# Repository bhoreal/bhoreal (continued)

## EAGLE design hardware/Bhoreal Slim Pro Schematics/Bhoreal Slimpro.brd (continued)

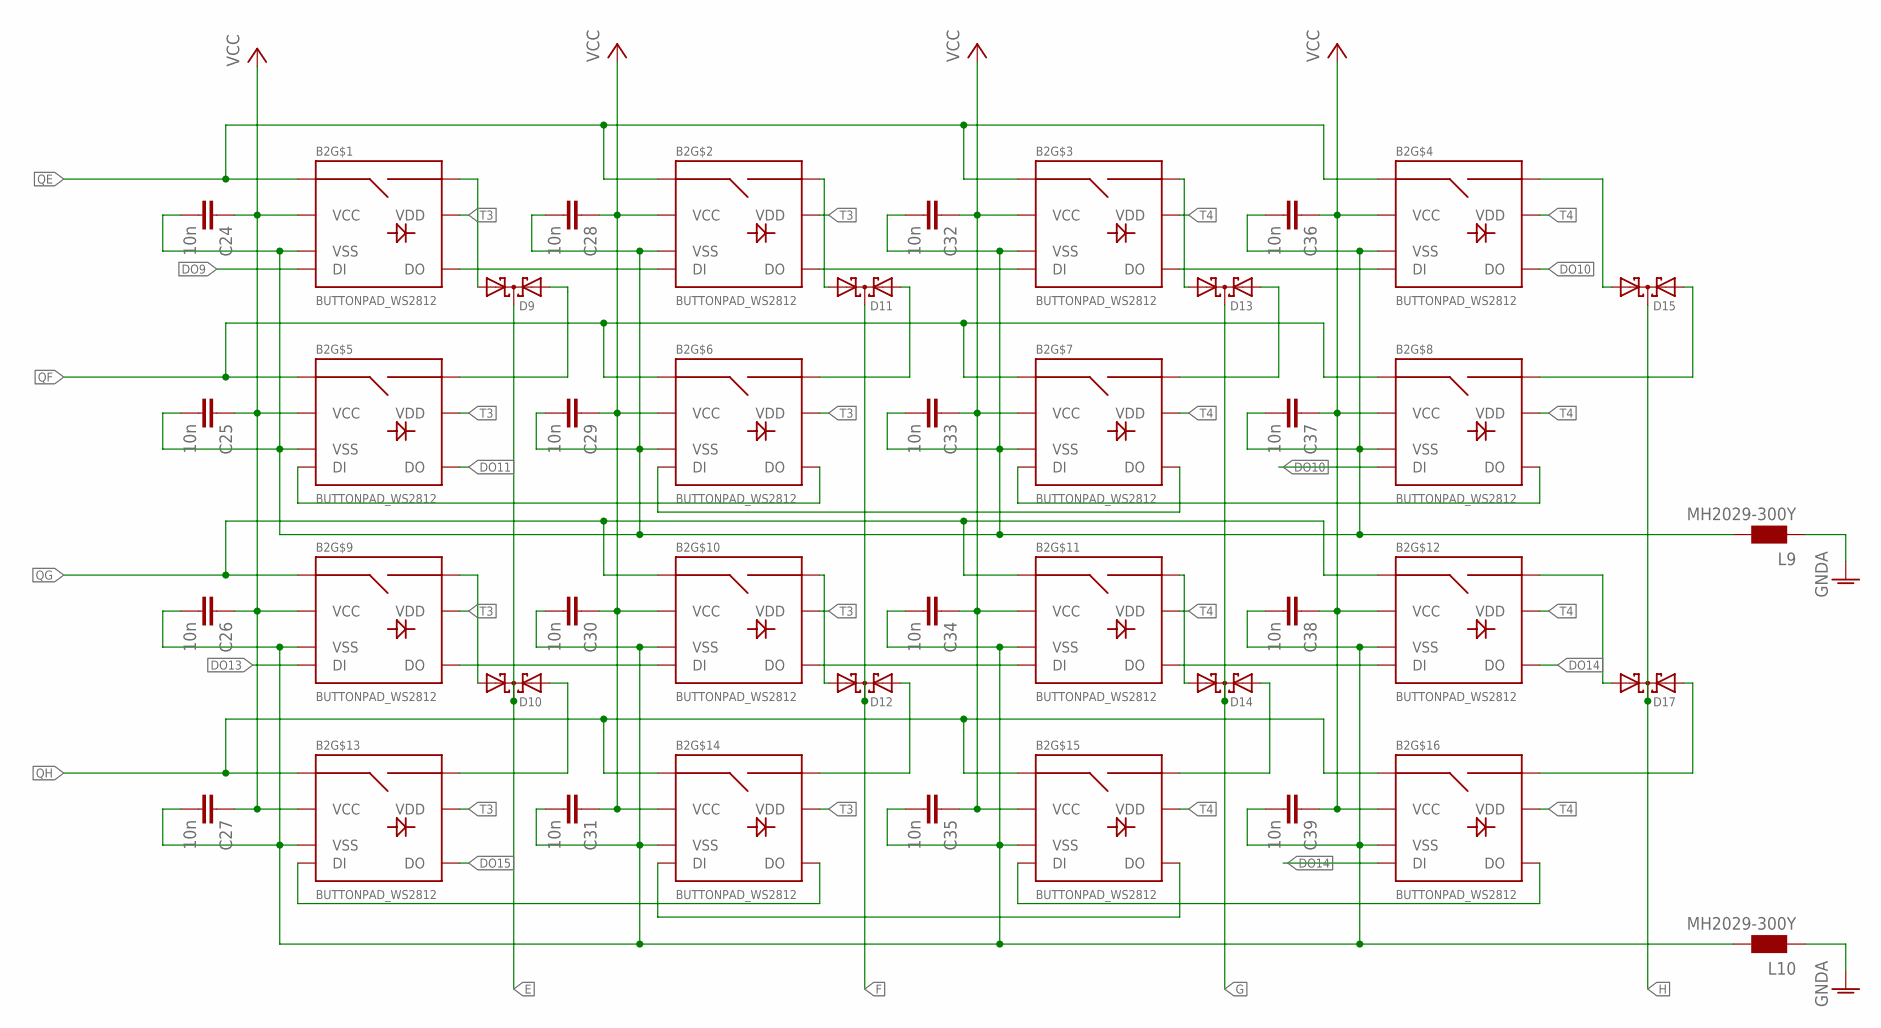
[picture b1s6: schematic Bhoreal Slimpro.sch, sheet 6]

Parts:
B2: BUTTONPAD_WS2812
C24, C25, C26, C27, C28, C29, C30, C31, C32, C33, C34, C35, C36, C37, C38, C39: 10n; C0603
D9, D10, D11, D12, D13, D14, D15, D17: BAV70LT3G; SOT23
L9, L10: MH2029-300Y; 0805

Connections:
DO9: B2.2A (DI); also elsewhere on the board
DO10: B2.1D (DO), B2.2H (DI)
DO11: B2.1E (DO); also elsewhere on the board
DO13: B2.2I (DI); also elsewhere on the board
DO14: B2.1L (DO), B2.2P (DI)
DO15: B2.1M (DO); also elsewhere on the board
E: D9.3 (C), D10.3 (C); also elsewhere on the board
F: D11.3 (C), D12.3 (C); also elsewhere on the board
G: D13.3 (C), D14.3 (C); also elsewhere on the board
GNDA: L9.1, L10.1; also elsewhere on the board
H: D15.3 (C), D17.3 (C); also elsewhere on the board
unnamed: B2.1A (DO), B2.2B (DI)
unnamed: B2.1B (DO), B2.2C (DI)
unnamed: B2.1C (DO), B2.2D (DI)
unnamed: B2.1K (DO), B2.2L (DI)
unnamed: B2.1J (DO), B2.2K (DI)
unnamed: B2.1I (DO), B2.2J (DI)
unnamed: B2.1F (DO), B2.2E (DI)
unnamed: B2.1G (DO), B2.2F (DI)
unnamed: B2.1H (DO), B2.2G (DI)
unnamed: B2.1P (DO), B2.2O (DI)
unnamed: B2.1O (DO), B2.2N (DI)
unnamed: B2.1N (DO), B2.2M (DI)
unnamed: B2.SIG2A (SIG2), D9.1 (A1)
unnamed: B2.SIG2E (SIG2), D9.2 (A2)
unnamed: B2.SIG2I (SIG2), D10.1 (A1)
unnamed: B2.SIG2M (SIG2), D10.2 (A2)
unnamed: B2.SIG2B (SIG2), D11.1 (A1)
unnamed: B2.SIG2F (SIG2), D11.2 (A2)
unnamed: B2.SIG2J (SIG2), D12.1 (A1)
unnamed: B2.SIG2N (SIG2), D12.2 (A2)
unnamed: B2.SIG2C (SIG2), D13.1 (A1)
unnamed: B2.SIG2G (SIG2), D13.2 (A2)
unnamed: B2.SIG2K (SIG2), D14.1 (A1)
unnamed: B2.SIG2O (SIG2), D14.2 (A2)
unnamed: B2.SIG2L (SIG2), D17.1 (A1)
unnamed: B2.SIG2P (SIG2), D17.2 (A2)
unnamed: B2.SIG2D (SIG2), D15.1 (A1)
unnamed: B2.SIG2H (SIG2), D15.2 (A2)
unnamed: B2.6I (VSS), B2.6J (VSS), B2.6K (VSS), B2.6L (VSS), B2.6M (VSS), B2.6N (VSS), B2.6O (VSS), B2.6P (VSS), C26.2, C27.2, C30.2, C31.2, C34.2, C35.2, C38.2, C39.2, L10.2
unnamed: B2.6A (VSS), B2.6B (VSS), B2.6C (VSS), B2.6D (VSS), B2.6E (VSS), B2.6F (VSS), B2.6G (VSS), B2.6H (VSS), C24.2, C25.2, C28.2, C29.2, C32.2, C33.2, C36.2, C37.2, L9.2
QE: B2.SIG1A (SIG1), B2.SIG1B (SIG1), B2.SIG1C (SIG1), B2.SIG1D (SIG1); also elsewhere on the board
QF: B2.SIG1E (SIG1), B2.SIG1F (SIG1), B2.SIG1G (SIG1), B2.SIG1H (SIG1); also elsewhere on the board
QG: B2.SIG1I (SIG1), B2.SIG1J (SIG1), B2.SIG1K (SIG1), B2.SIG1L (SIG1); also elsewhere on the board
QH: B2.SIG1M (SIG1), B2.SIG1N (SIG1), B2.SIG1O (SIG1), B2.SIG1P (SIG1); also elsewhere on the board
T3: B2.5A (VDD), B2.5B (VDD), B2.5E (VDD), B2.5F (VDD), B2.5I (VDD), B2.5J (VDD), B2.5M (VDD), B2.5N (VDD); also elsewhere on the board
T4: B2.5C (VDD), B2.5D (VDD), B2.5G (VDD), B2.5H (VDD), B2.5K (VDD), B2.5L (VDD), B2.5O (VDD), B2.5P (VDD); also elsewhere on the board
VCC: B2.3A (VCC), B2.3B (VCC), B2.3C (VCC), B2.3D (VCC), B2.3E (VCC), B2.3F (VCC), B2.3G (VCC), B2.3H (VCC), B2.3I (VCC), B2.3J (VCC), B2.3K (VCC), B2.3L (VCC), B2.3M (VCC), B2.3N (VCC), B2.3O (VCC), B2.3P (VCC), C24.1, C25.1, C26.1, C27.1, C28.1, C29.1, C30.1, C31.1, C32.1, C33.1, C34.1, C35.1, C36.1, C37.1, C38.1, C39.1; also elsewhere on the board

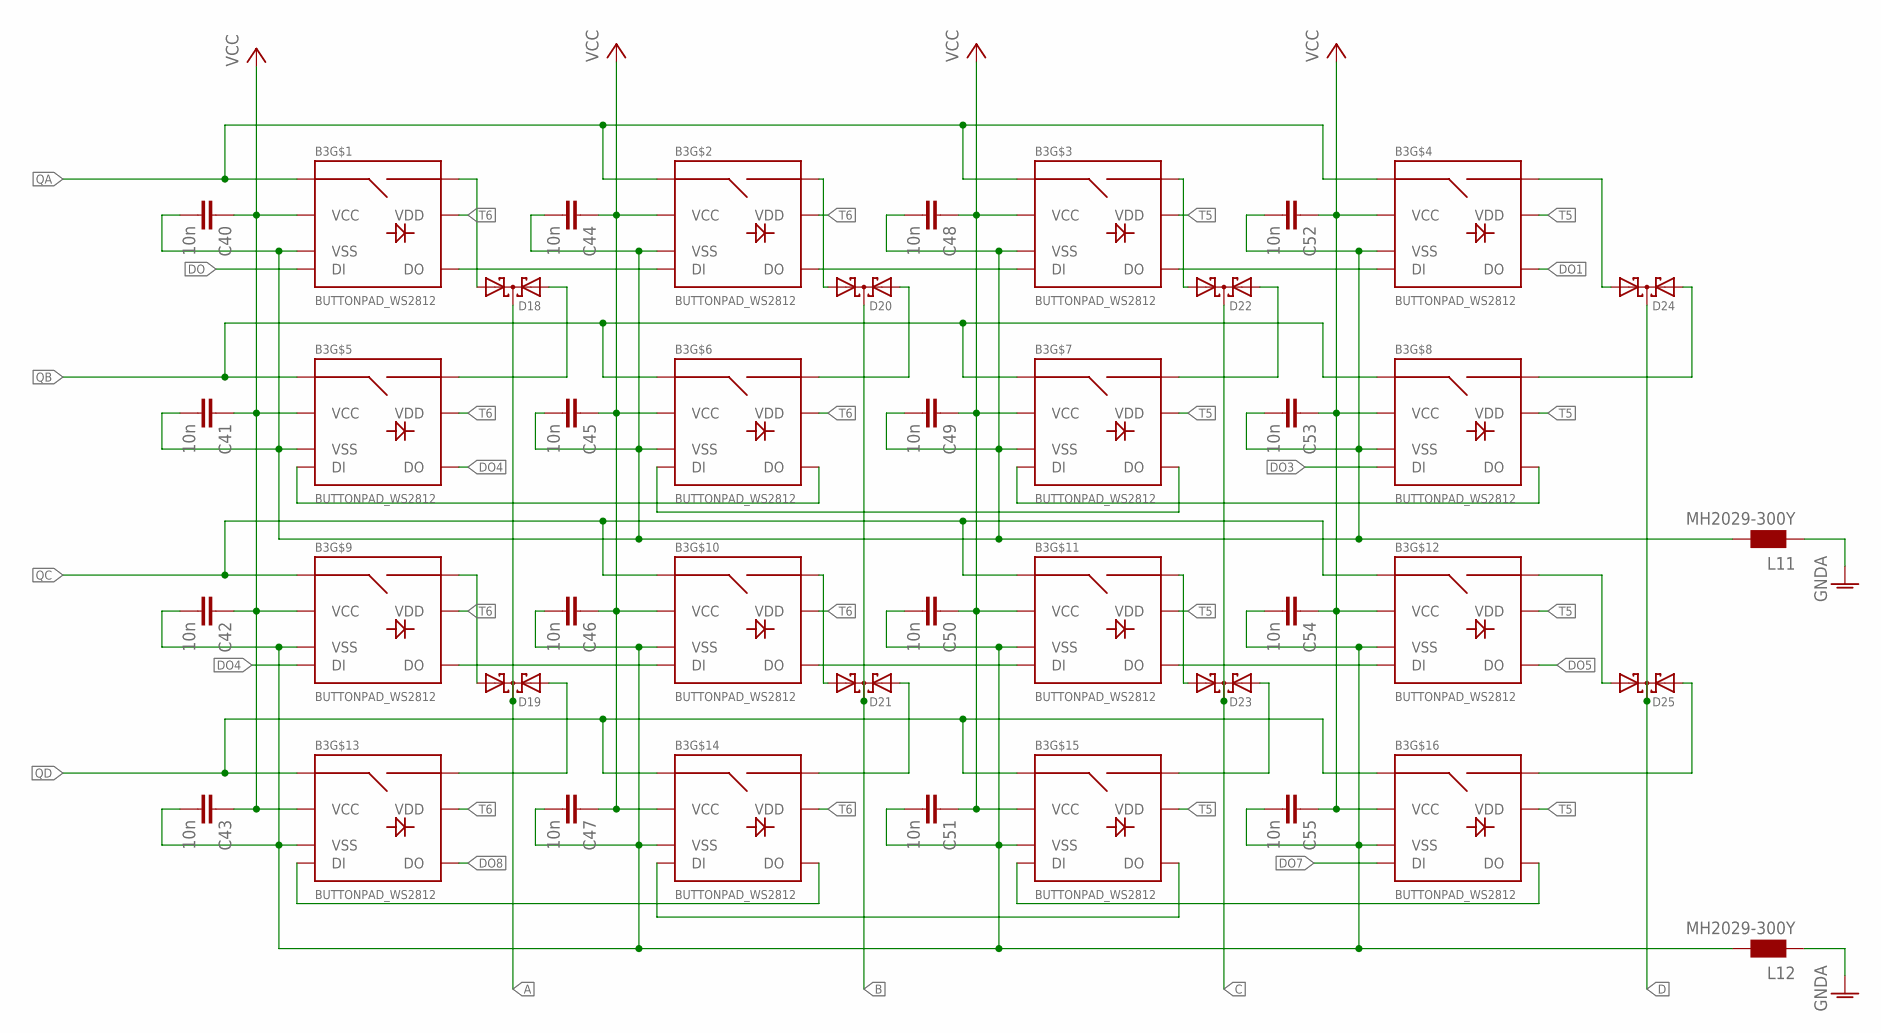
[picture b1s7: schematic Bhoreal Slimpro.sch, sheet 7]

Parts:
B3: BUTTONPAD_WS2812
C40, C41, C42, C43, C44, C45, C46, C47, C48, C49, C50, C51, C52, C53, C54, C55: 10n; C0603
D18, D19, D20, D21, D22, D23, D24, D25: BAV70LT3G; SOT23
L11, L12: MH2029-300Y; 0805

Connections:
A: D18.3 (C), D19.3 (C); also elsewhere on the board
B: D20.3 (C), D21.3 (C); also elsewhere on the board
C: D22.3 (C), D23.3 (C); also elsewhere on the board
D: D24.3 (C), D25.3 (C); also elsewhere on the board
DO: B3.2A (DI); also elsewhere on the board
DO1: B3.1D (DO); also elsewhere on the board
DO3: B3.2H (DI); also elsewhere on the board
DO4: B3.1E (DO), B3.2I (DI)
DO5: B3.1L (DO); also elsewhere on the board
DO7: B3.2P (DI); also elsewhere on the board
DO8: B3.1M (DO); also elsewhere on the board
GNDA: L11.1, L12.1; also elsewhere on the board
unnamed: B3.1A (DO), B3.2B (DI)
unnamed: B3.1B (DO), B3.2C (DI)
unnamed: B3.1C (DO), B3.2D (DI)
unnamed: B3.1K (DO), B3.2L (DI)
unnamed: B3.1J (DO), B3.2K (DI)
unnamed: B3.1I (DO), B3.2J (DI)
unnamed: B3.1F (DO), B3.2E (DI)
unnamed: B3.1G (DO), B3.2F (DI)
unnamed: B3.1H (DO), B3.2G (DI)
unnamed: B3.1P (DO), B3.2O (DI)
unnamed: B3.1O (DO), B3.2N (DI)
unnamed: B3.1N (DO), B3.2M (DI)
unnamed: B3.SIG2A (SIG2), D18.1 (A1)
unnamed: B3.SIG2E (SIG2), D18.2 (A2)
unnamed: B3.SIG2I (SIG2), D19.1 (A1)
unnamed: B3.SIG2M (SIG2), D19.2 (A2)
unnamed: B3.SIG2B (SIG2), D20.1 (A1)
unnamed: B3.SIG2F (SIG2), D20.2 (A2)
unnamed: B3.SIG2J (SIG2), D21.1 (A1)
unnamed: B3.SIG2N (SIG2), D21.2 (A2)
unnamed: B3.SIG2C (SIG2), D22.1 (A1)
unnamed: B3.SIG2G (SIG2), D22.2 (A2)
unnamed: B3.SIG2K (SIG2), D23.1 (A1)
unnamed: B3.SIG2O (SIG2), D23.2 (A2)
unnamed: B3.SIG2L (SIG2), D25.1 (A1)
unnamed: B3.SIG2P (SIG2), D25.2 (A2)
unnamed: B3.SIG2D (SIG2), D24.1 (A1)
unnamed: B3.SIG2H (SIG2), D24.2 (A2)
unnamed: B3.6A (VSS), B3.6B (VSS), B3.6C (VSS), B3.6D (VSS), B3.6E (VSS), B3.6F (VSS), B3.6G (VSS), B3.6H (VSS), C40.2, C41.2, C44.2, C45.2, C48.2, C49.2, C52.2, C53.2, L11.2
unnamed: B3.6I (VSS), B3.6J (VSS), B3.6K (VSS), B3.6L (VSS), B3.6M (VSS), B3.6N (VSS), B3.6O (VSS), B3.6P (VSS), C42.2, C43.2, C46.2, C47.2, C50.2, C51.2, C54.2, C55.2, L12.2
QA: B3.SIG1A (SIG1), B3.SIG1B (SIG1), B3.SIG1C (SIG1), B3.SIG1D (SIG1); also elsewhere on the board
QB: B3.SIG1E (SIG1), B3.SIG1F (SIG1), B3.SIG1G (SIG1), B3.SIG1H (SIG1); also elsewhere on the board
QC: B3.SIG1I (SIG1), B3.SIG1J (SIG1), B3.SIG1K (SIG1), B3.SIG1L (SIG1); also elsewhere on the board
QD: B3.SIG1M (SIG1), B3.SIG1N (SIG1), B3.SIG1O (SIG1), B3.SIG1P (SIG1); also elsewhere on the board
T5: B3.5C (VDD), B3.5D (VDD), B3.5G (VDD), B3.5H (VDD), B3.5K (VDD), B3.5L (VDD), B3.5O (VDD), B3.5P (VDD); also elsewhere on the board
T6: B3.5A (VDD), B3.5B (VDD), B3.5E (VDD), B3.5F (VDD), B3.5I (VDD), B3.5J (VDD), B3.5M (VDD), B3.5N (VDD); also elsewhere on the board
VCC: B3.3A (VCC), B3.3B (VCC), B3.3C (VCC), B3.3D (VCC), B3.3E (VCC), B3.3F (VCC), B3.3G (VCC), B3.3H (VCC), B3.3I (VCC), B3.3J (VCC), B3.3K (VCC), B3.3L (VCC), B3.3M (VCC), B3.3N (VCC), B3.3O (VCC), B3.3P (VCC), C40.1, C41.1, C42.1, C43.1, C44.1, C45.1, C46.1, C47.1, C48.1, C49.1, C50.1, C51.1, C52.1, C53.1, C54.1, C55.1; also elsewhere on the board

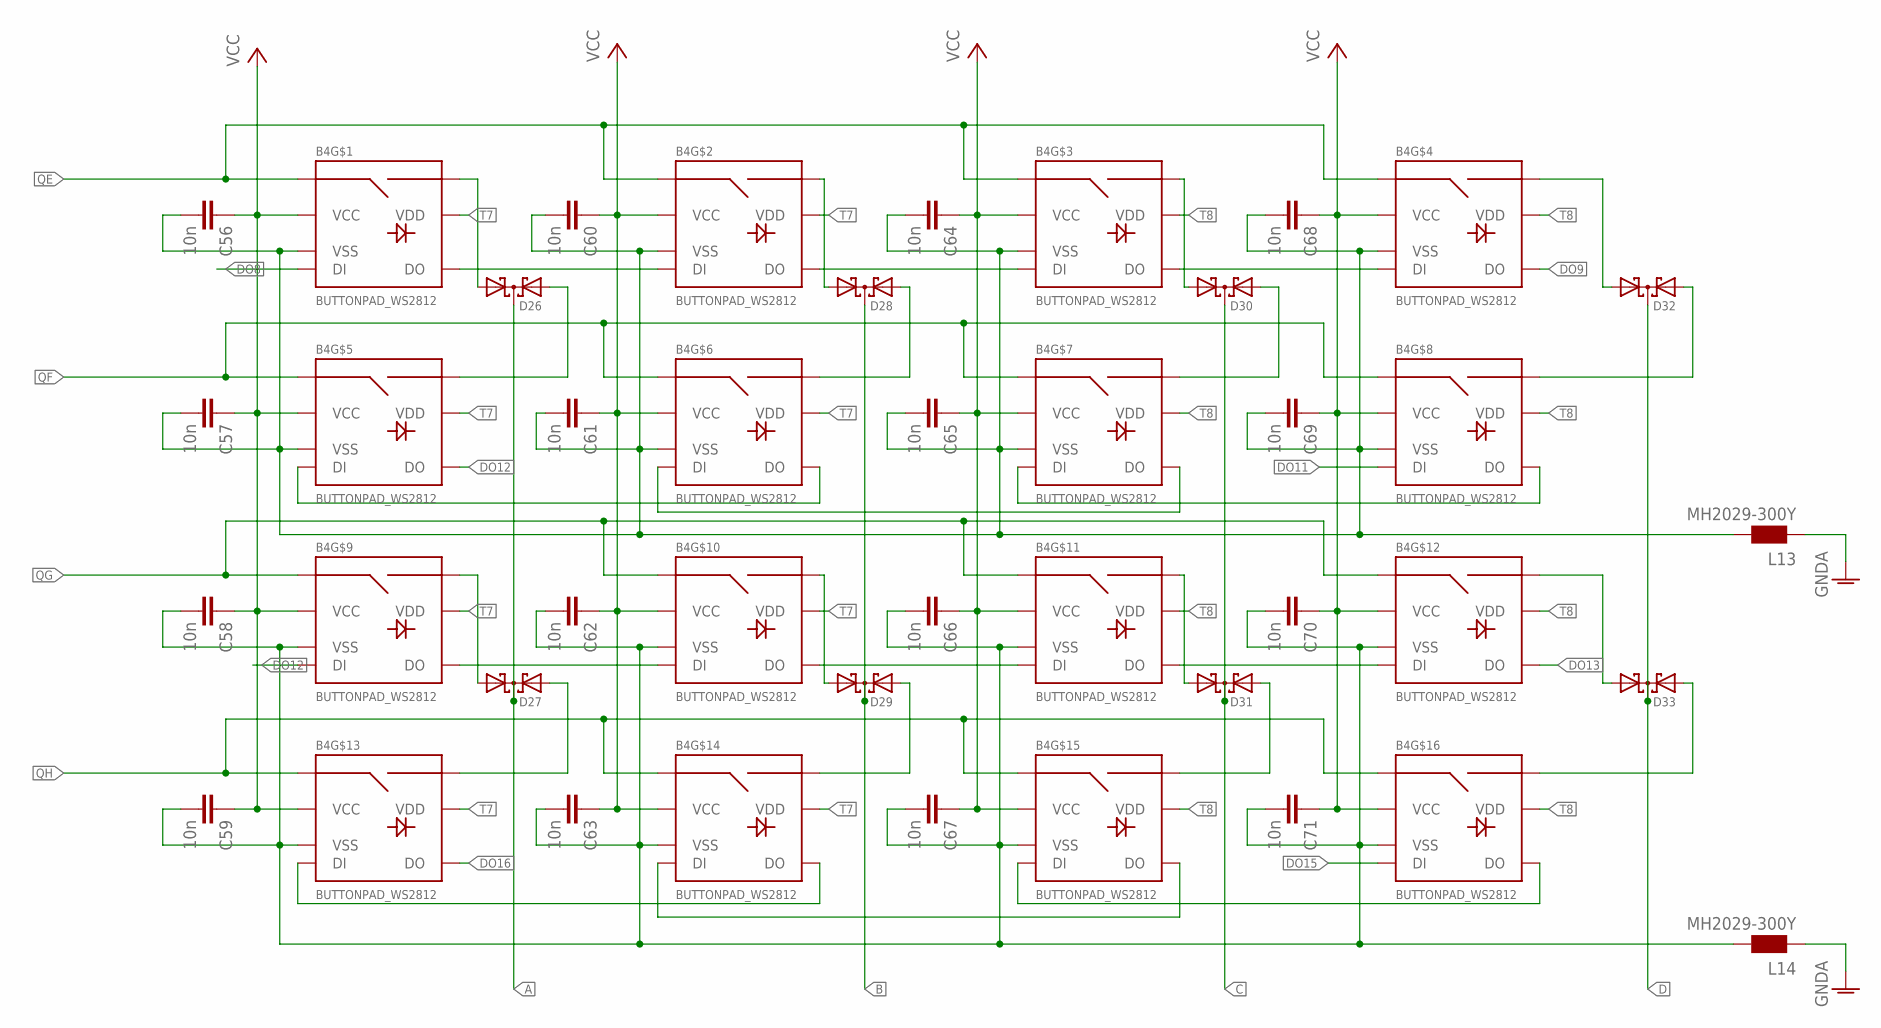
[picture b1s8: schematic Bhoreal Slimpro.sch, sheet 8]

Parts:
B4: BUTTONPAD_WS2812
C56, C57, C58, C59, C60, C61, C62, C63, C64, C65, C66, C67, C68, C69, C70, C71: 10n; C0603
D26, D27, D28, D29, D30, D31, D32, D33: BAV70LT3G; SOT23
L13, L14: MH2029-300Y; 0805

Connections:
A: D26.3 (C), D27.3 (C); also elsewhere on the board
B: D28.3 (C), D29.3 (C); also elsewhere on the board
C: D30.3 (C), D31.3 (C); also elsewhere on the board
D: D32.3 (C), D33.3 (C); also elsewhere on the board
DO8: B4.2A (DI); also elsewhere on the board
DO9: B4.1D (DO); also elsewhere on the board
DO11: B4.2H (DI); also elsewhere on the board
DO12: B4.1E (DO), B4.2I (DI)
DO13: B4.1L (DO); also elsewhere on the board
DO15: B4.2P (DI); also elsewhere on the board
DO16: B4.1M (DO)
GNDA: L13.1, L14.1; also elsewhere on the board
unnamed: B4.1A (DO), B4.2B (DI)
unnamed: B4.1B (DO), B4.2C (DI)
unnamed: B4.1C (DO), B4.2D (DI)
unnamed: B4.1K (DO), B4.2L (DI)
unnamed: B4.1J (DO), B4.2K (DI)
unnamed: B4.1I (DO), B4.2J (DI)
unnamed: B4.1F (DO), B4.2E (DI)
unnamed: B4.1G (DO), B4.2F (DI)
unnamed: B4.1H (DO), B4.2G (DI)
unnamed: B4.1P (DO), B4.2O (DI)
unnamed: B4.1O (DO), B4.2N (DI)
unnamed: B4.1N (DO), B4.2M (DI)
unnamed: B4.SIG2A (SIG2), D26.1 (A1)
unnamed: B4.SIG2E (SIG2), D26.2 (A2)
unnamed: B4.SIG2I (SIG2), D27.1 (A1)
unnamed: B4.SIG2M (SIG2), D27.2 (A2)
unnamed: B4.SIG2B (SIG2), D28.1 (A1)
unnamed: B4.SIG2F (SIG2), D28.2 (A2)
unnamed: B4.SIG2J (SIG2), D29.1 (A1)
unnamed: B4.SIG2N (SIG2), D29.2 (A2)
unnamed: B4.SIG2C (SIG2), D30.1 (A1)
unnamed: B4.SIG2G (SIG2), D30.2 (A2)
unnamed: B4.SIG2K (SIG2), D31.1 (A1)
unnamed: B4.SIG2O (SIG2), D31.2 (A2)
unnamed: B4.SIG2L (SIG2), D33.1 (A1)
unnamed: B4.SIG2P (SIG2), D33.2 (A2)
unnamed: B4.SIG2D (SIG2), D32.1 (A1)
unnamed: B4.SIG2H (SIG2), D32.2 (A2)
unnamed: B4.6I (VSS), B4.6J (VSS), B4.6K (VSS), B4.6L (VSS), B4.6M (VSS), B4.6N (VSS), B4.6O (VSS), B4.6P (VSS), C58.2, C59.2, C62.2, C63.2, C66.2, C67.2, C70.2, C71.2, L14.2
unnamed: B4.6A (VSS), B4.6B (VSS), B4.6C (VSS), B4.6D (VSS), B4.6E (VSS), B4.6F (VSS), B4.6G (VSS), B4.6H (VSS), C56.2, C57.2, C60.2, C61.2, C64.2, C65.2, C68.2, C69.2, L13.2
QE: B4.SIG1A (SIG1), B4.SIG1B (SIG1), B4.SIG1C (SIG1), B4.SIG1D (SIG1); also elsewhere on the board
QF: B4.SIG1E (SIG1), B4.SIG1F (SIG1), B4.SIG1G (SIG1), B4.SIG1H (SIG1); also elsewhere on the board
QG: B4.SIG1I (SIG1), B4.SIG1J (SIG1), B4.SIG1K (SIG1), B4.SIG1L (SIG1); also elsewhere on the board
QH: B4.SIG1M (SIG1), B4.SIG1N (SIG1), B4.SIG1O (SIG1), B4.SIG1P (SIG1); also elsewhere on the board
T7: B4.5A (VDD), B4.5B (VDD), B4.5E (VDD), B4.5F (VDD), B4.5I (VDD), B4.5J (VDD), B4.5M (VDD), B4.5N (VDD); also elsewhere on the board
T8: B4.5C (VDD), B4.5D (VDD), B4.5G (VDD), B4.5H (VDD), B4.5K (VDD), B4.5L (VDD), B4.5O (VDD), B4.5P (VDD); also elsewhere on the board
VCC: B4.3A (VCC), B4.3B (VCC), B4.3C (VCC), B4.3D (VCC), B4.3E (VCC), B4.3F (VCC), B4.3G (VCC), B4.3H (VCC), B4.3I (VCC), B4.3J (VCC), B4.3K (VCC), B4.3L (VCC), B4.3M (VCC), B4.3N (VCC), B4.3O (VCC), B4.3P (VCC), C56.1, C57.1, C58.1, C59.1, C60.1, C61.1, C62.1, C63.1, C64.1, C65.1, C66.1, C67.1, C68.1, C69.1, C70.1, C71.1; also elsewhere on the board

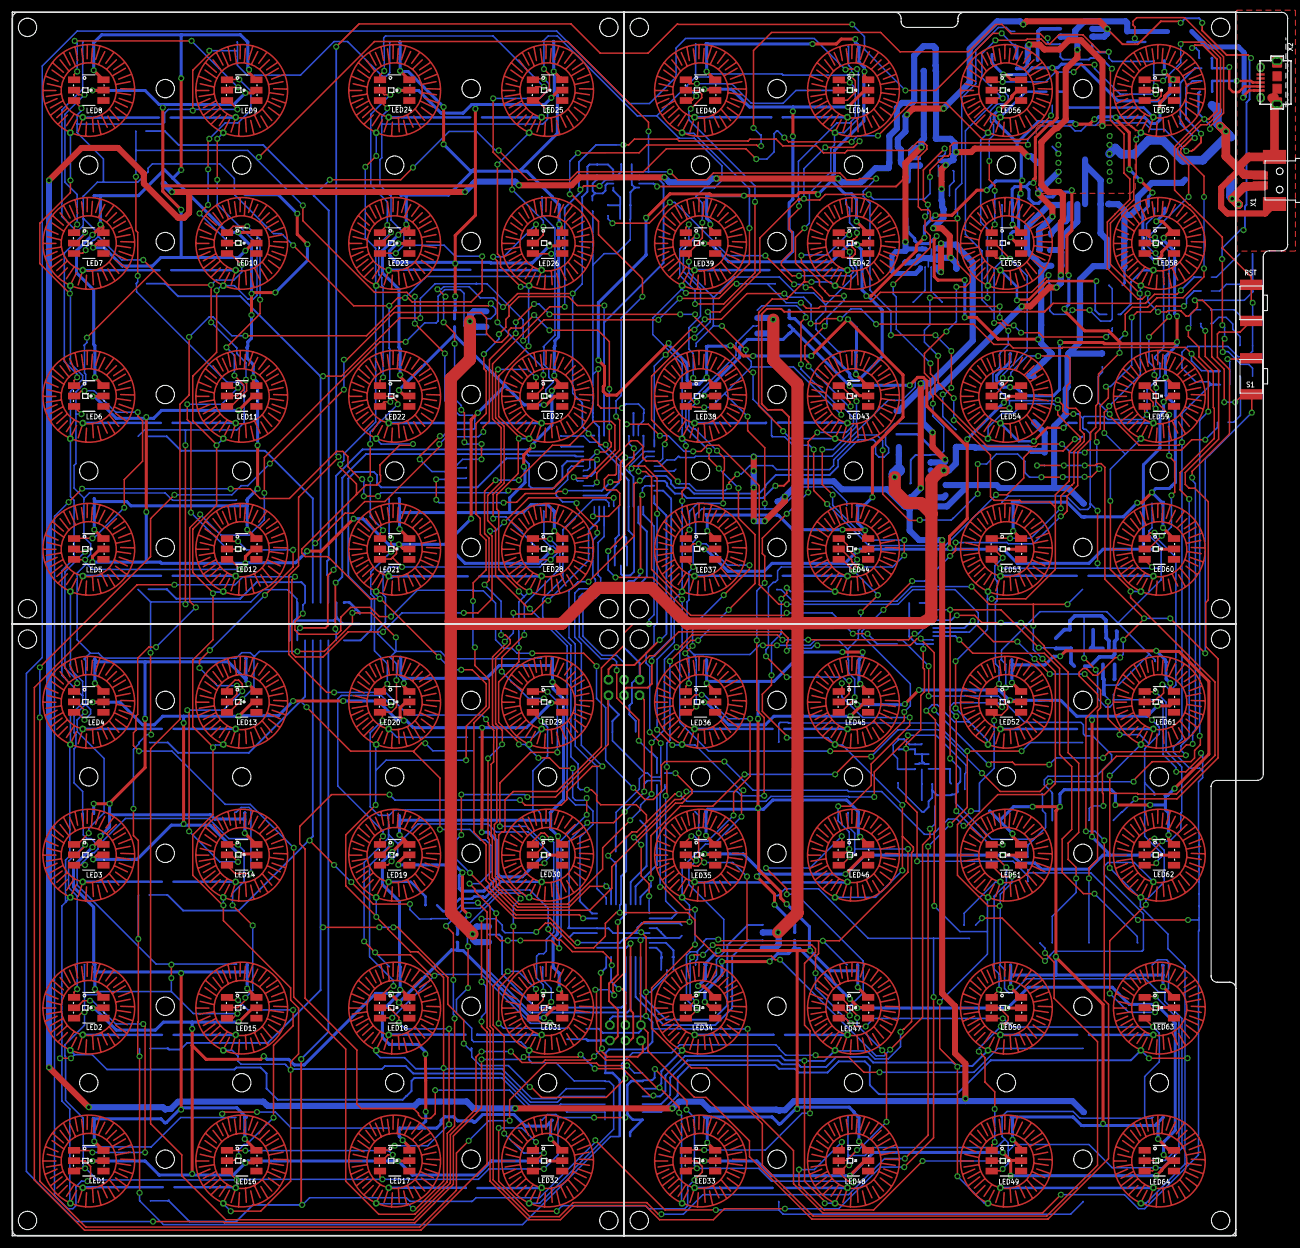
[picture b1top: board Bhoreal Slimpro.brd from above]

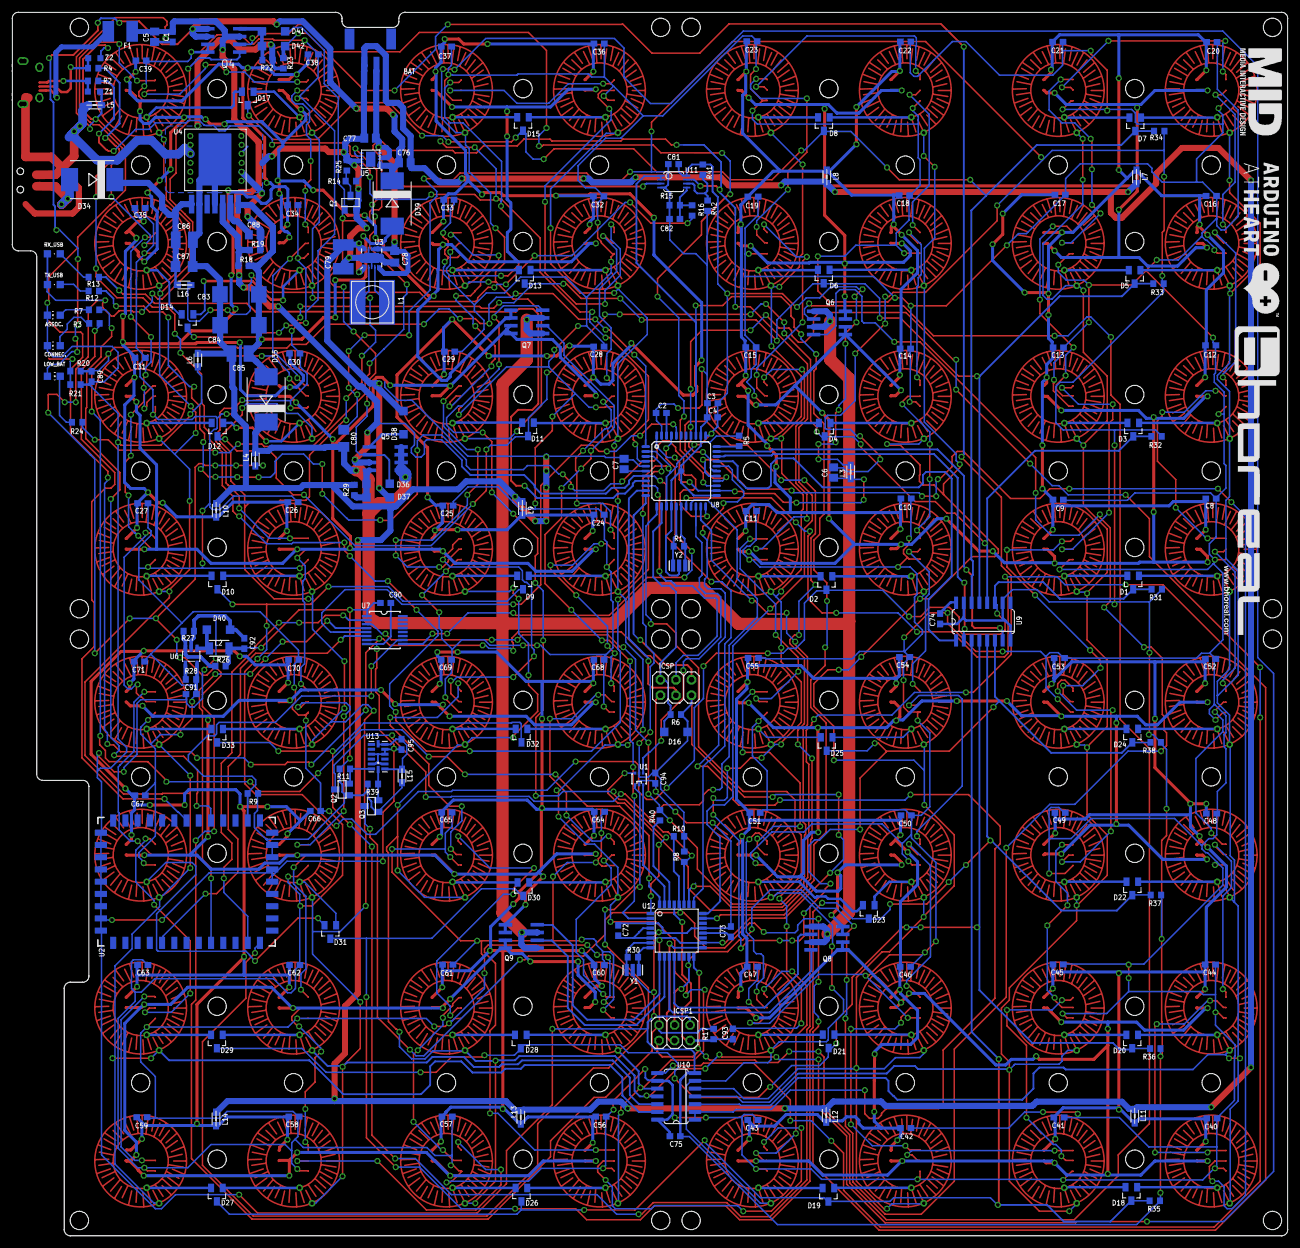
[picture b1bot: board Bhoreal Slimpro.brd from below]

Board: 2 copper layers, 208.5 x 200.0 mm, 238 parts (230 on the bottom side), 255 nets.

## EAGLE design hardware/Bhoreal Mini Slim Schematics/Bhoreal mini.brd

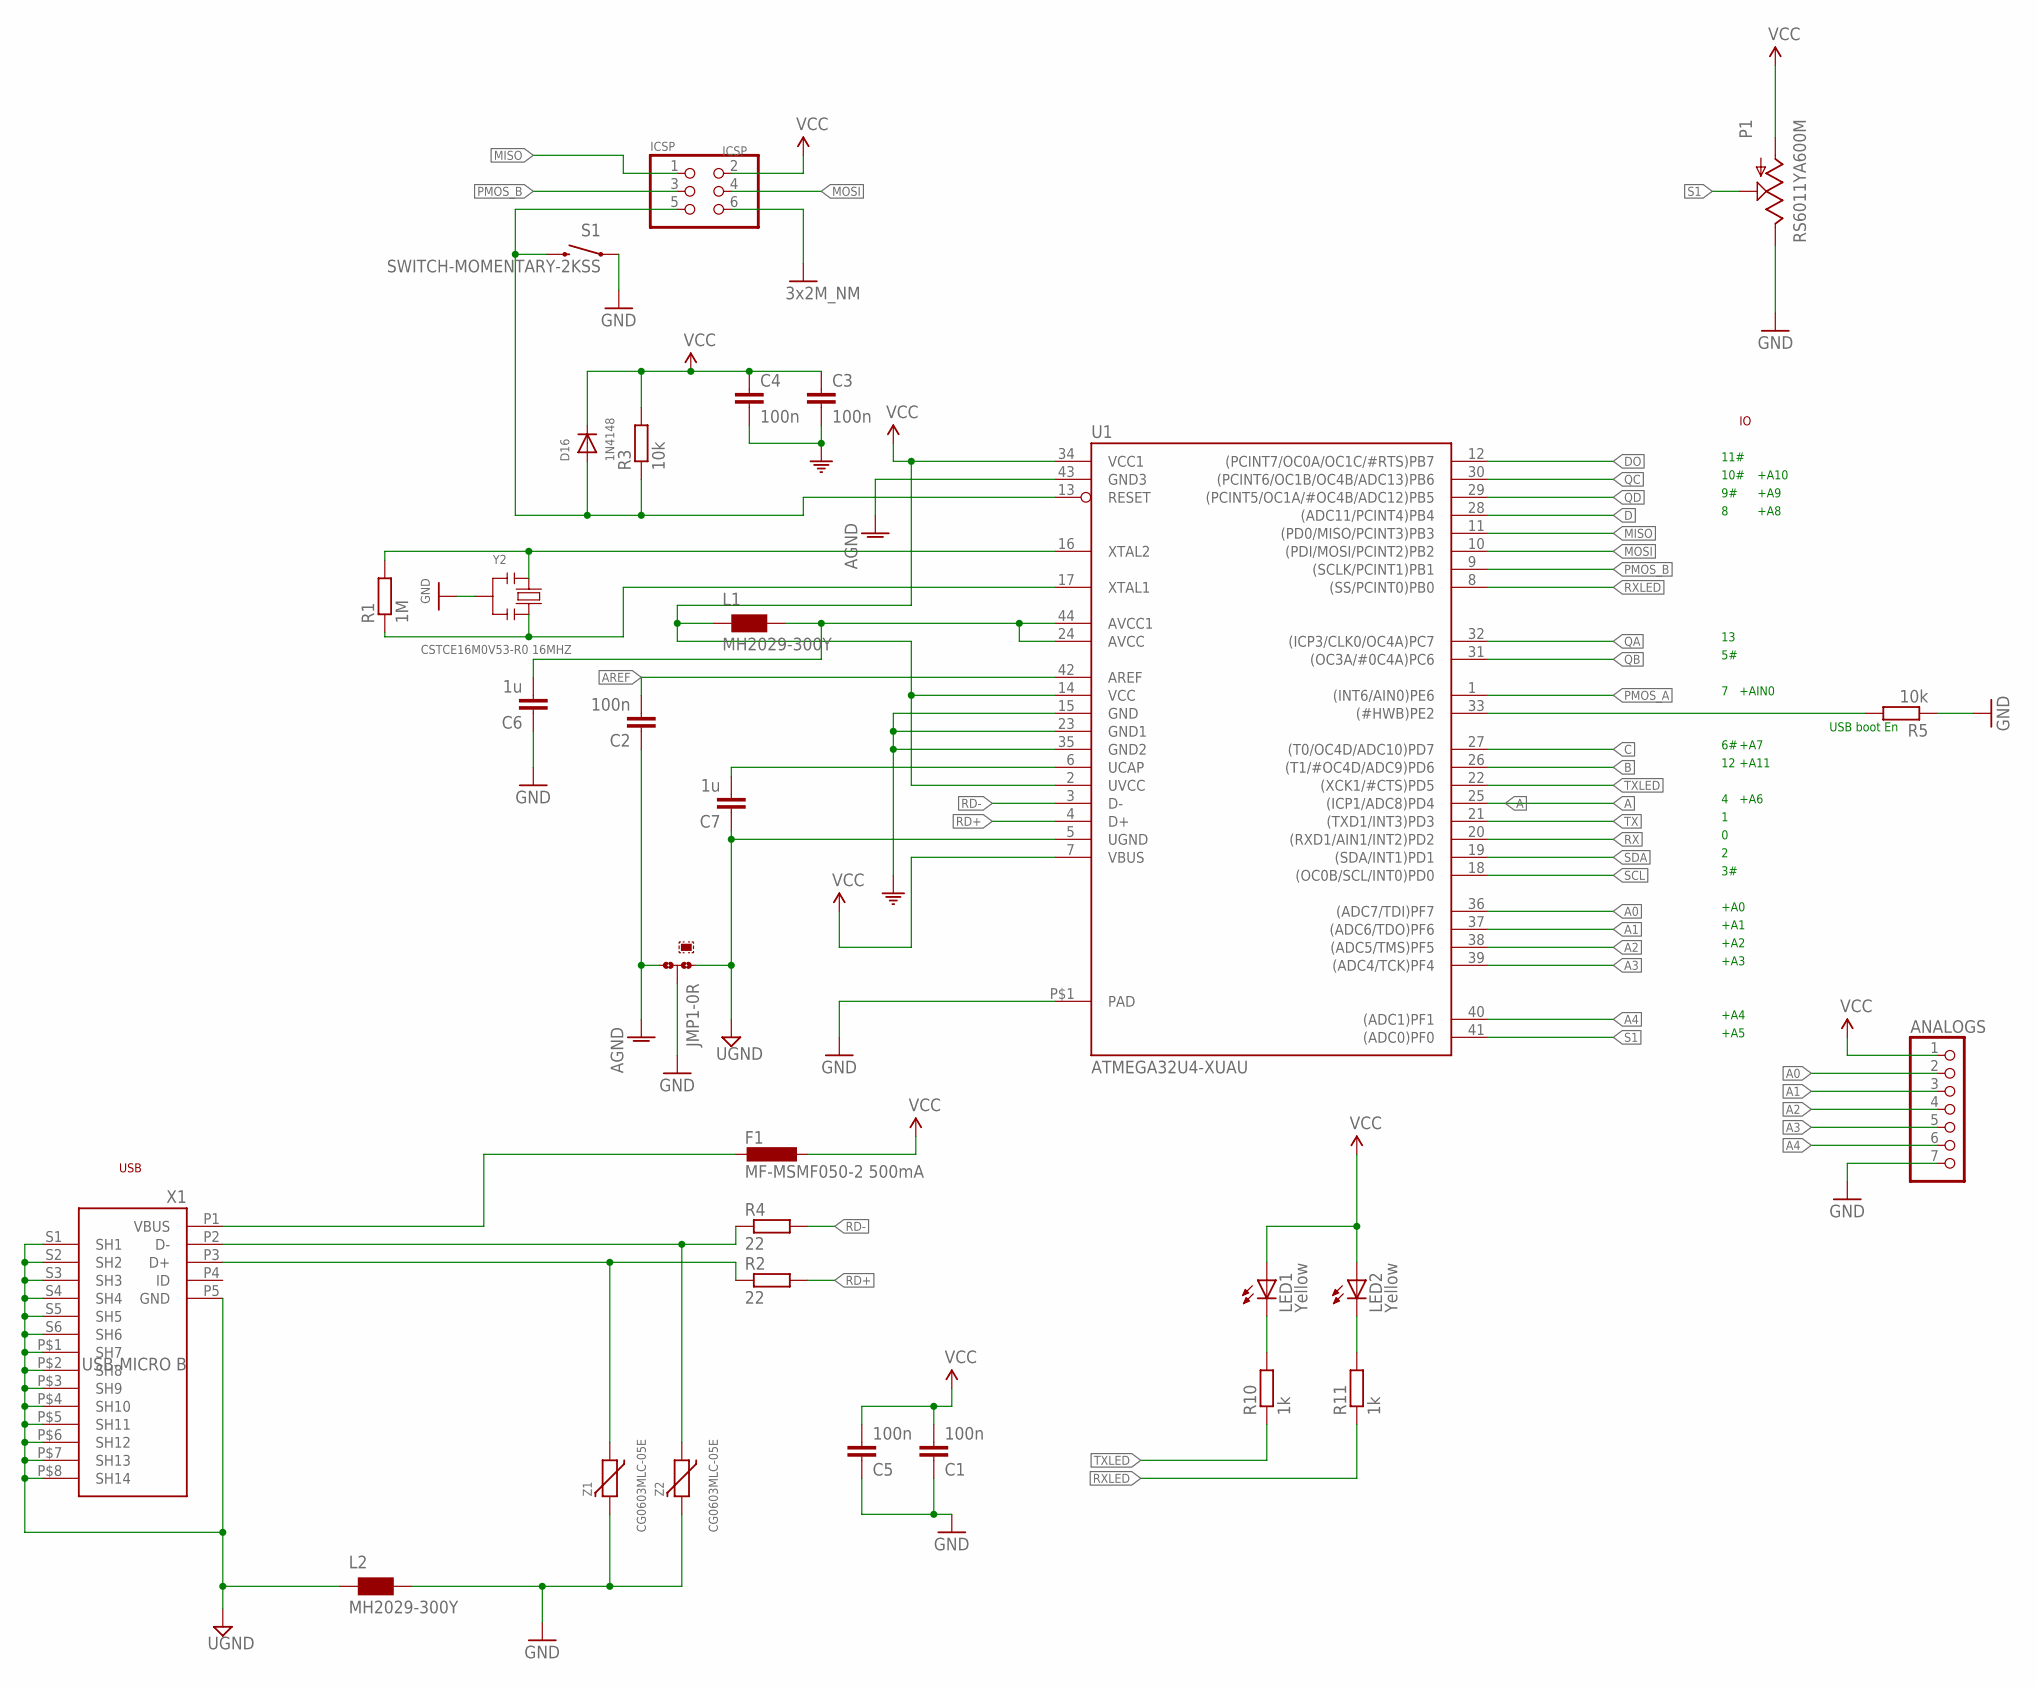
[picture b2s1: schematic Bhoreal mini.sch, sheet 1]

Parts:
ANALOGS: PINHD-1X7; 1X07
C1, C2, C3, C4, C5: 100n; C0603K
C6, C7: 1u; C0805
D16: 1N4148; SOD-323F
F1: MF-MSMF050-2 500mA; L1812
ICSP: ICSP; 2X03
JMP1: 0R-JUMPC; C0R-JMP
L1, L2: MH2029-300Y; 0805
LED1, LED2: Yellow; CHIPLED_0805
P1: RS6011YA600M
R1: 1M; R0603
R2, R4: 22; R0603
R3, R5: 10k; R0603
R10, R11: 1k; R0603
S1: SWITCH-MOMENTARY-2KSS; KSS241G
U1: ATMEGA32U4-XUAU; TQFP44-PAD
X1: USB-MICRO B; CON2_USB_MICRO_B_AT
Y2: CSTCE16M0V53-R0 16MHZ; RESONATOR
Z1, Z2: CG0603MLC-05E; CT/CN0603

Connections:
A: U1.25 ((ICP1/ADC8)PD4); also elsewhere on the board
A0: ANALOGS.2, U1.36 ((ADC7/TDI)PF7)
A1: ANALOGS.3, U1.37 ((ADC6/TDO)PF6)
A2: ANALOGS.4, U1.38 ((ADC5/TMS)PF5)
A3: ANALOGS.5, U1.39 ((ADC4/TCK)PF4)
A4: ANALOGS.6, U1.40 ((ADC1)PF1)
AGND: C2.1, JMP1.3, U1.43 (GND3)
AREF: C2.2, U1.42 (AREF)
AVCC: C6.2, L1.2, U1.24 (AVCC), U1.44 (AVCC1)
B: U1.26 ((T1/#OC4D/ADC9)PD6); also elsewhere on the board
C: U1.27 ((T0/OC4D/ADC10)PD7); also elsewhere on the board
D: U1.28 ((ADC11/PCINT4)PB4); also elsewhere on the board
D+: R2.1, X1.P3 (D+), Z1.1
D-: R4.1, X1.P2 (D-), Z2.1
DO: U1.12 ((PCINT7/OC0A/OC1C/#RTS)PB7); also elsewhere on the board
GND: ANALOGS.7, C1.1, C3.2, C4.2, C5.1, C6.1, ICSP.6, JMP1.2, L2.2, P1.2 (E), R5.1, S1.1, U1.15 (GND), U1.23 (GND1), U1.35 (GND2), U1.P$1 (PAD), Y2.2, Z1.2, Z2.2; also elsewhere on the board
HWB: R5.2, U1.33 ((#HWB)PE2)
MISO: ICSP.1, U1.11 ((PD0/MISO/PCINT3)PB3)
MOSI: ICSP.4, U1.10 ((PDI/MOSI/PCINT2)PB2)
unnamed: LED1.C, R10.2
unnamed: LED2.C, R11.2
PMOS_A: U1.1 ((INT6/AIN0)PE6); also elsewhere on the board
PMOS_B: ICSP.3, U1.9 ((SCLK/PCINT1)PB1); also elsewhere on the board
QA: U1.32 ((ICP3/CLK0/OC4A)PC7); also elsewhere on the board
QB: U1.31 ((OC3A/#0C4A)PC6); also elsewhere on the board
QC: U1.30 ((PCINT6/OC1B/OC4B/ADC13)PB6); also elsewhere on the board
QD: U1.29 ((PCINT5/OC1A/#OC4B/ADC12)PB5); also elsewhere on the board
RD+: R2.2, U1.4 (D+)
RD-: R4.2, U1.3 (D-)
RESET: D16.A, ICSP.5, R3.1, S1.2, U1.13 (RESET)
RX: U1.20 ((RXD1/AIN1/INT2)PD2)
RXLED: R11.1, U1.8 ((SS/PCINT0)PB0)
S1: P1.1 (S), U1.41 ((ADC0)PF0)
SCL: U1.18 ((OC0B/SCL/INT0)PD0)
SDA: U1.19 ((SDA/INT1)PD1)
TX: U1.21 ((TXD1/INT3)PD3)
TXLED: R10.1, U1.22 ((XCK1/#CTS)PD5)
UCAP: C7.2, U1.6 (UCAP)
UGND: C7.1, JMP1.1, L2.1, U1.5 (UGND), X1.P5 (GND), X1.P$1 (SH7), X1.P$2 (SH8), X1.P$3 (SH9), X1.P$4 (SH10), X1.P$5 (SH11), X1.P$6 (SH12), X1.P$7 (SH13), X1.P$8 (SH14), X1.S1 (SH1), X1.S2 (SH2), X1.S3 (SH3), X1.S4 (SH4), X1.S5 (SH5), X1.S6 (SH6)
VCC: ANALOGS.1, C1.2, C3.1, C4.1, C5.2, D16.C, F1.1, ICSP.2, L1.1, LED1.A, LED2.A, P1.3 (A), R3.2, U1.2 (UVCC), U1.7 (VBUS), U1.14 (VCC), U1.34 (VCC1); also elsewhere on the board
XTAL3: R1.2, U1.16 (XTAL2), Y2.1
XTAL4: R1.1, U1.17 (XTAL1), Y2.3
XUSB: F1.2, X1.P1 (VBUS)

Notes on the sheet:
USB boot En
USB
10#
11#
+A6
+A11
+A10
+A9
+A7
+A8
+AIN0
+A0
+A1
+A2
+A3
+A4
+A5
